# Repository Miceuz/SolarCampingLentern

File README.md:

# Open source Solar Camping Lantern

## Background

I started seeing a lot of disposable electronic cigarettes being used. As everyone knows, those devices contain perfectly rechargeable LiPo battery. And I've seen them thrown away everywhere - on streets, in general waste thrash cans, etc. While a lot of my friends have successfully refilled juice and re-charged the battery, the devices are not built to last - heating coil dies after several re-uses anyway. I have decided to look for a way to recycle those batteries. 

So I have decided to make a lantern for my camping needs and also investigate a product parameter space. The idea popped in to my mind during a summer music festival, actually. When you camp with your friends and need a bit of extra light in the camp at night. It was a sunny summer, so of course I had to have it solar powered. Provided unlimited supply of batteries, can it be self sufficient in it's power needs just from solar energy while still being manageable in camp environment?

It's always a good idea to check what's available at the market. Maybe there is a product on the market that does just that? Just a piece of my expenses, not worth spending my time?

## Initial requirements

 * Light output: ~100lm
 * Run time: min 4h
 * Battery: LiPo 3.7V ~2000mAh
 * Charging time: 6h

I have gauged the amount of needed light from my Lumilight pocket torch I have lost and my "cyclope" torch from Decathlon I got this year. 100lm is not a huge amount of light but still not that bad - it's enough to see people and stuff around, human eye is logarithmic and adapts to low light conditions.

Run time is a modest guess from a festival scenario - you might need light from 11 at night to 3 in the morning, roughly.

Charging time is a lazy day camping, maybe I will remember to pull it out and put on a sun sometime. It's not full effective sun time, just general time the device spends in sun semi-kinda-charging.

## Case studies

### [BioLite SunLight 100](https://www.bioliteenergy.com/products/sunlight-100?variant=1142597386254)

  * Light output: 100lm max
  * Battery: 750mAh LiPo
  * Run time: 3h
  * Solar pannel: 0.45W
  * Charging time: 7h
  * Dimensions: 85x86x23 mm
  * Weight: 95g
  * Price: 20$

### [MPOWERD Luci Outdoor 2.0](https://mpowerd.com/products/luci-outdoor-2-0-f2017)

 * Light output: 75lm
 * Battery: 1000mAh
 * Run time: 6h
 * Charging time: 7h
 * Dimensions: 127mm dia, 25mm height
 * Weight: 125g
 * Price: 24$

### [MPowerd Luci Solar String Lights](https://mpowerd.com/products/string-lights)

 * Light output: 100lm
 * Battery: 2000mAh
 * Charging time: 16h
 * Run time: 5h
 * Dimensions: 127mm dia, 50mm height
 * Weight: 320g
 * Price: 50$

There are devices that target the same light output I want. Some of these specifications are inferred as not all manufacturers provide all the information I needed. SunLight 100 does almost exactly what I want, but solar battery this size barely will produce 8.3Wh needed in 7h of charging time. All in all solar in all of these products seems to be a nice addition to USB charging, not the main power provider. 

Also I have bought some not-so-cheap crap from local hardware store that pretended like it can do what I want, but solar battery was total crap in those, outputting mere single digit milli-amps.

Thus, I have easily convinced myself that this is well worth as a hobby project. Besides, had to use those batteries up! So, with the battery sourcing question sorted out, let's not think about price too much and look what happens if we push on the light output efficiency and solar input efficiency.

## Design

### MPPT options

 * SPV1040T
 * ADP5090ACPZ-2-R7
 * BQ24650
 * [MPPT Solar Panel Controller with DC Converter](https://www.tindie.com/products/electronicstore/mppt-solar-panel-controller-with-dc-converter-2)

In the times of supply chain collapse, choosing a MMPT capable converter chip for storing solar energy to the battery was not an easy thing. They all are either not available or expensive. Luckily I have stumbled on this board by [PC Tech](https://www.tindie.com/stores/electronicstore/) featuring CN3791. Basically this project could have ended just there, as this board was all I needed - I have made my first prototype using it. Although I had to extract a bit more efficiency by having a dedicated led driver, also add some computer control to the thing. 

### Light Source

 * L130-4070003000W21 - Vf = 6V, I = 100mA, Light output = 100lm

It's one of the most efficient LEDs available at electronic distributors at the time. What's interesting and handy is that it's practically voltage controlled - it has a nice shallow IV curve. Provided you extract the heat from them though. They will happily do 100lm at 0.6W, the efficiency is even higher if you run them at half the rating. That's why I have doubled them up in my design.

Also I have decided to throw in a red light source, to see if it might be usable too. Red light does not dazzle humans too much, so it makes a good low level standby light source for the night. I did not want to add additional complication of channel switching for led driver chip, thus decided to power red led directly from MCU pin.

### Photovoltaics

 * [Solar panel](https://www.evita.lt/u-9045-saules-baterijos-modulis-6v-3-5w-165x135mm?search=saul%C4%97s) 6V, 3.5W

These panels, available at local suppliers, looked like a good trade-off between size and output power. Besides, not a lot to choose from, really. I have measured them and they were outputting the rated power, but it dropped drastically with non-perfect orientation to the sun, thus it has to be de-rated significantly. I have guesstimated MPPT point of the panel to be somewhere at 80% of it's open circuit voltage and measured about the same with a potentiometer hooked up to it.

### Power

**If you replicate this design, be warned that battery failure is a risk to be considered!**

 * Battery: 3.7 LiPo, capacity varies: 1.4Wh, 1.85Wh, total capacity up to 11Wh
 * MCU powered directly from battery
 * DC-DC led driver - MCP1664

Batteries are re-used from electronic cigarettes. I don't really know if they retain their safety ratings after they have been re-charged, but people around are re-charging them and I've heard of no fires happening. 

They come with a protection board and I have tried shorting and over-discharging them - seem to work fine, also I've seen my friends ridiculously abusing them with high charge currents on par of 3C. Their longevity is to be proven though as they might not be optimized for a lot of re-charge cycles, but it seems their safety is on par with standards mandatory with CE marking. I am happy to delay their travel to a landfill or a recycler.  

### Operational parameters

 * Energy consumed: 0.1A * 6V * 4h = 2.4Wh
 * Solar power available: 3.5W minus conversion losses
 * Light output: 120lm

It has plenty of solar - 1h of perfect sunlight should provide enough of charge for 4 required hours. Seems to make sense to have more battery capacity, but there is a small trade-off with the weight. It will be interesting to experiment with battery sizes and see what run times are achievable.

### Mechanical construction

Size and shape of the device is dictated by the solar panel. Since I wanted a lot of solar power, I knew I will not be able to make it as compact as commercially available devices. Also mechanical side of things is not my strength, so I went for a simple flat panel. One of use cases for such a light would be as a coaster for a water bottle - that makes a pretty nice low effort table light. Also I've added 4 holes to attach the lantern with rope - to a branch or a tarp. 

All assembly is glue based (blergh!). Batteries are glued to the PCB. PCB is glued and soldered to the solar panel. Both the solar panel and plexiglass are glued to a 3D printed plastic frame.

Considering the usage scenario, of course it should have some level of ingress protection. Provided all glue seams are tight (sic!), the only place for water to seep in is through a button hole. I am going to experiment with printing of the frame from flexible plastics and have the button hole closed, but for the first revision there's going to be a small seam between hole and plunger and IPX6 rated button behind it.

### MCU and software

I have chosen my beloved attiny441 - I have a stock of them and I am used to them and it's a relief to spend some time in a simple naive world of 8-bit microcontrollers. It's pretty low power too.

Software functions:

 * On/Off
 * Different levels of lighting
 * Cycle through white and red leds
 * Indicate battery level via charlieplexed leds
 * Auto level reduction on low battery [todo]
 * Fade everywhere [todo]
 * Sky's the limit, what can you do with a single button interface?

### Bells and whistles

 * Charlieplexed leds for battery level indication

### Weight analysis

| Item | Weight, g |
|------|-----------|
| 3.5W solar panel | 96 |
| Plexiglass | 73 |
| Frame | 56 |
| PCB 0.8mm | 36 |
| Battery 380mAh 7g, 3pack | 22 |
| Electronic components | 4 |
| Glue | 10 |
| **Total** | **297** |

## BOM Price analysis

| Item | Price, € |
|------|----------|
| Solar panel | 13 |
| Electronic components | 6.3 |
| PCB | 5.1 |
| Frame | 2 |
| Plexiglass | 0.6 |
| Batteries | 0 |
| **Total** | **27** | 

Prices are for a small batch of 10 units.

## Final specifications

 * Light output: 120lm
 * Battery: LiPo 3.7V up to 4000mAh 
 * Run time: >4h
 * Solar pannel: 3.5W
 * Charging time for 4h run time: 1h (perfect sun conditions)
 * Dimensions: 193x163x15 mm
 * Weight: 297g
 * BOM Price: 27€

## Conclusion

I took me 3 PCB iterations to get it right, I had to adjust a button position so it's easier to find in the dark, also I had to spread battery level indication leds along the edge so they would be distinguishable behind the plexiglass. Finally I have used 4 while leds instead of two, also spaced out as the single light source was a bit too strong. 

Weight is a concern, but here I am limited to materials I have access to. I have made some improvements by using a 0.8mm PCB, maybe I can make the frame lighter, but the real limiting factors are solar pannel and plexiglass.

I have tried using the first prototype while camping at sunny autumn and it proved to be working very well. Working time with 870mAh battery was a little too short for long autumn evenings at full 100lm, but it was able to fully charge during the next day. Later I brought the panel to a rainy camping trip in December. Panel was barely charging the 5.5Ah battery, but it held almost two evenings allowing us to set up camp, prepare wood and chill under the red light in addition to fire. I think it's not much useful for rainy winter in Easter Europe, but it will be a perfect light for summer camping.

## Licence

[CERN Open Hardware Licence Version 2 - Strongly Reciprocal](https://ohwr.org/cern_ohl_s_v2.txt)

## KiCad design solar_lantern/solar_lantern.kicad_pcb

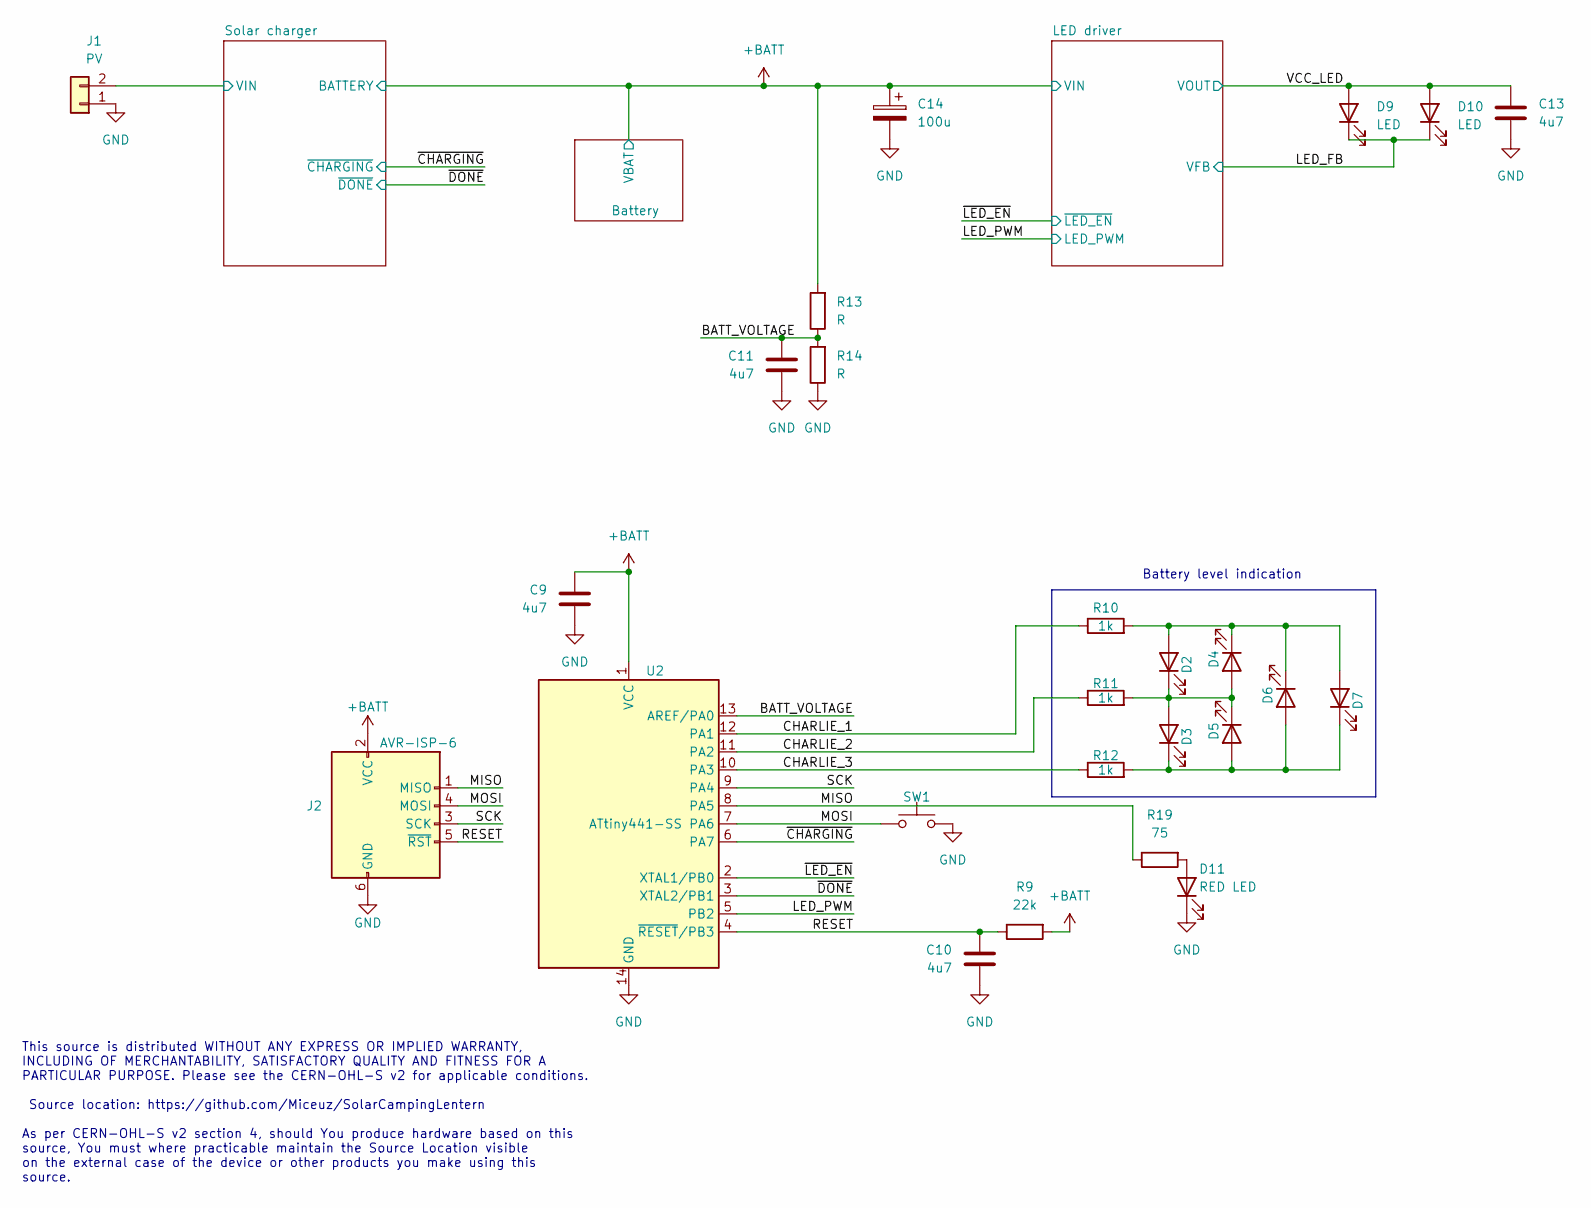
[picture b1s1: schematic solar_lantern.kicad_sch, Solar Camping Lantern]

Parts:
C9, C10, C11, C13: 4u7; C_0603_1608Metric
C14: 100u; CP_Elec_6.3x5.4_Nichicon; PartNo EEV107M016S9GAA
D2, D3, D4, D5, D6, D7: LED; D_0603_1608Metric
D9, D10: LED; DS207; PartNo L130-4070003000W21
D11: RED LED; LED_PLCC-2; PartNo CLM1B-RKW-CUbVbAA3
J1: PV; PinHeader_1x02_P2.54mm_Vertical
J2: AVR-ISP-6; PinHeader_2x03_P2.54mm_Vertical
R9: 22k; R_0603_1608Metric
R10, R11, R12: 1k; R_0603_1608Metric
R13, R14: R; R_0603_1608Metric
R19: 75; R_0603_1608Metric
SW1: SW_Push; SW_Push_1P1T_NO_6x6mm_H9.5mm; PartNo 1571407-2
U2: ATtiny441-SS; SOIC-14_3.9x8.7mm_P1.27mm

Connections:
+BATT: C9.2, C14.1, J2.2 (VCC), R9.2, R13.2, U2.1 (VCC); also elsewhere on the board
/BATT_VOLTAGE: C11.2, R13.1, R14.2, U2.13 (AREF/PA0)
/CHARLIE_1: R10.1, U2.12 (PA1)
/CHARLIE_2: R11.1, U2.11 (PA2)
/CHARLIE_3: R12.1, U2.10 (PA3)
/LED_FB: D9.1 (K), D10.1 (K); also elsewhere on the board
/LED_PWM: U2.5 (PB2); also elsewhere on the board
/MISO: J2.1 (MISO), R19.1, U2.8 (PA5)
/MOSI: J2.4 (MOSI), SW1.1, U2.7 (PA6)
/RESET: C10.2, J2.5 (~RST), R9.1, U2.4 (~RESET/PB3)
/SCK: J2.3 (SCK), U2.9 (PA4)
/Solar charger/VIN: J1.2; also elsewhere on the board
/VCC_LED: C13.1, D9.2 (A), D10.2 (A); also elsewhere on the board
/~CHARGING: U2.6 (PA7); also elsewhere on the board
/~DONE: U2.3 (XTAL2/PB1); also elsewhere on the board
/~LED_EN: U2.2 (XTAL1/PB0); also elsewhere on the board
GND: C9.1, C10.1, C11.1, C13.2, C14.2, D11.2 (K), J1.1, J2.6 (GND), R14.1, SW1.2, U2.14 (GND); also elsewhere on the board
unnamed: D2.1 (K), D3.2 (A), D4.2 (A), D5.1 (K), R11.2
unnamed: D2.2 (A), D4.1 (K), D6.1 (K), D7.2 (A), R10.2
unnamed: D3.1 (K), D5.2 (A), D6.2 (A), D7.1 (K), R12.2
unnamed: D11.1 (A), R19.2

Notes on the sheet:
This source is distributed WITHOUT ANY EXPRESS OR IMPLIED WARRANTY, INCLUDING OF MERCHANTABILITY, SATISFACTORY QUALITY AND FITNESS FOR A PARTICULAR PURPOSE. Please see the CERN-OHL-S v2 for applicable conditions. Source location: https://github.com/Miceuz/SolarCampingLentern As per CERN-OHL-S v2 se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
Battery level indication

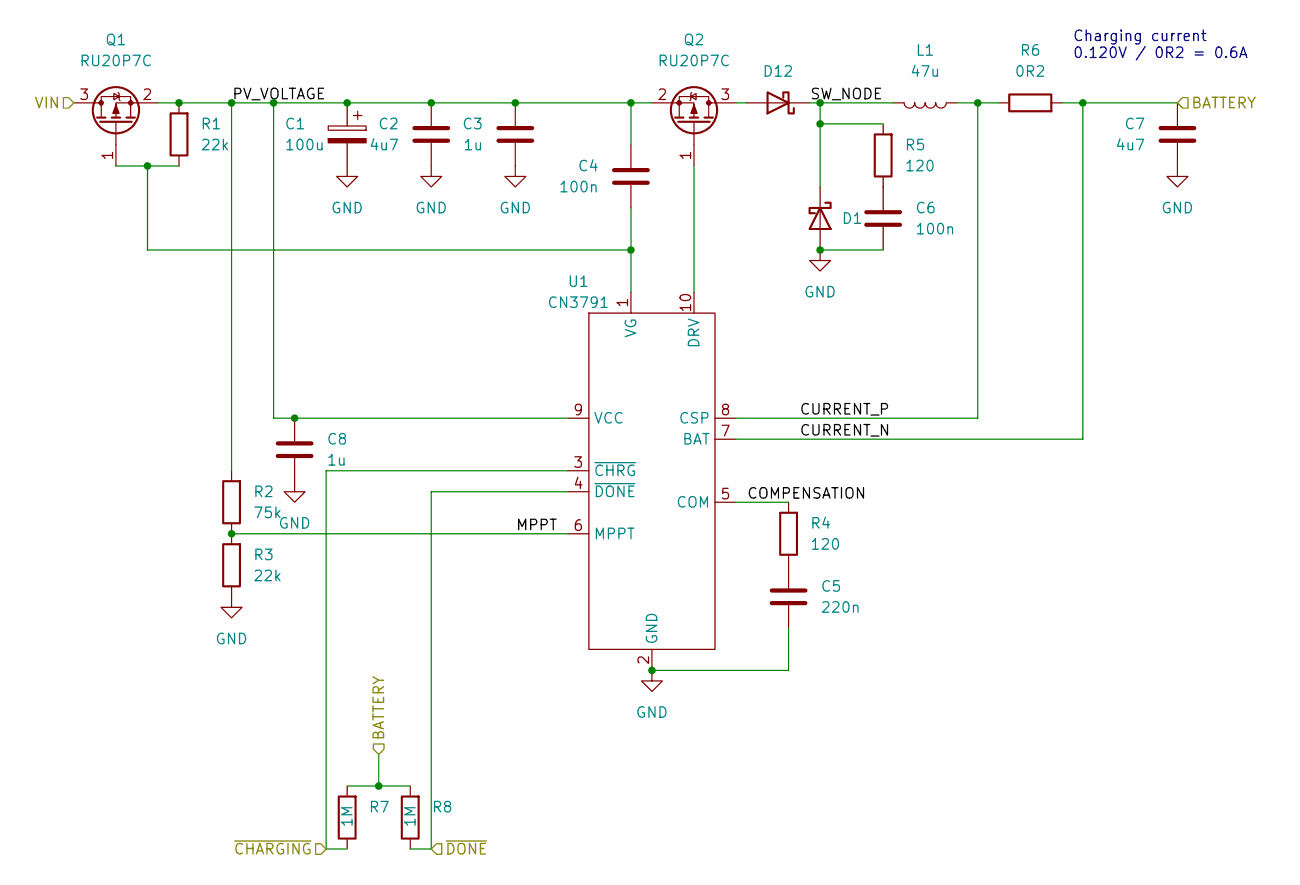
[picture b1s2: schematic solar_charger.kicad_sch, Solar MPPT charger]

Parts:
C1: 100u; CP_Elec_6.3x5.4_Nichicon; PartNo EEV107M016S9GAA
C2, C7: 4u7; C_0603_1608Metric
C3, C8: 1u; C_0402_1005Metric
C4, C6: 100n; C_0603_1608Metric
C5: 220n; C_0603_1608Metric
D1, D12: D_Schottky; D_SOD-323
L1: 47u; L_Coilcraft_XAL60xx_6.36x6.56mm
Q1, Q2: RU20P7C; SOT-23
R1, R3: 22k; R_0603_1608Metric
R2: 75k; R_0603_1608Metric
R4, R5: 120; R_0603_1608Metric
R6: 0R2; R_2512_6332Metric
R7, R8: 1M; R_0603_1608Metric
U1: CN3791; SSOP-10_3.9x4.9mm_P1.00mm

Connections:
+BATT: C7.2, R6.2, R7.2, R8.2, U1.7 (BAT); also elsewhere on the board
/Solar charger/COMPENSATION: R4.2, U1.5 (COM)
/Solar charger/CURRENT_P: L1.2, R6.1, U1.8 (CSP)
/Solar charger/MPPT: R2.1, R3.2, U1.6 (MPPT)
/Solar charger/PV_VOLTAGE: C1.1, C2.2, C3.2, C4.2, C8.2, Q1.2 (S), Q2.2 (S), R1.2, R2.2, U1.9 (VCC)
/Solar charger/SW_NODE: D1.1 (K), D12.1 (K), L1.1, R5.2
/Solar charger/VIN: Q1.3 (D); also elsewhere on the board
/~CHARGING: R7.1, U1.3 (~CHRG); also elsewhere on the board
/~DONE: R8.1, U1.4 (~DONE); also elsewhere on the board
GND: C1.2, C2.1, C3.1, C5.1, C6.1, C7.1, C8.1, D1.2 (A), R3.1, U1.2 (GND); also elsewhere on the board
unnamed: C4.1, Q1.1 (G), R1.1, U1.1 (VG)
unnamed: C5.2, R4.1
unnamed: C6.2, R5.1
unnamed: Q2.1 (G), U1.10 (DRV)
unnamed: D12.2 (A), Q2.3 (D)

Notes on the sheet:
Charging current 0.120V / 0R2 = 0.6A

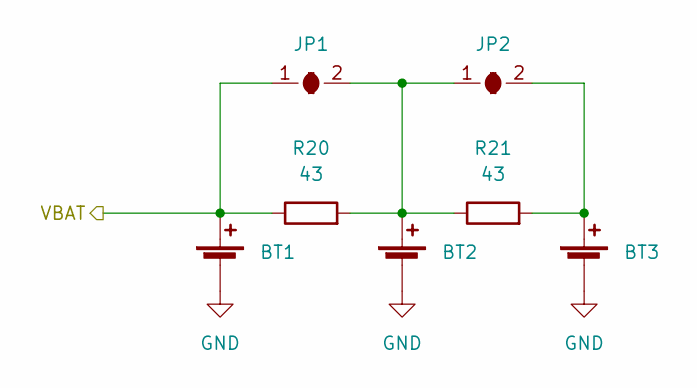
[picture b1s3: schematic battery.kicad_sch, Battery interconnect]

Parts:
BT1, BT2, BT3: Battery_Cell; PinHeader_1x02_P2.54mm_Vertical
JP1, JP2: SolderJumper_2_Open; SolderJumper-2_P1.3mm_Open_TrianglePad1.0x1.5mm
R20, R21: 43; R_0603_1608Metric; PartNo SDR03EZPJ430

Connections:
+BATT: BT1.1 (+), JP1.1 (A), R20.1; also elsewhere on the board
GND: BT1.2 (-), BT2.2 (-), BT3.2 (-); also elsewhere on the board
unnamed: BT2.1 (+), JP1.2 (B), JP2.1 (A), R20.2, R21.1
unnamed: BT3.1 (+), JP2.2 (B), R21.2

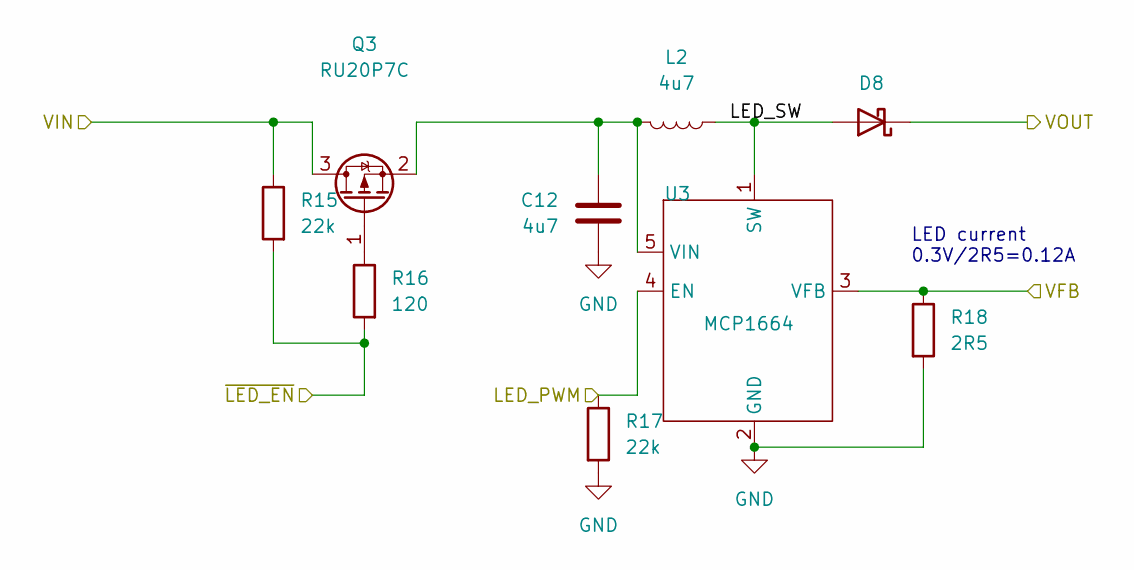
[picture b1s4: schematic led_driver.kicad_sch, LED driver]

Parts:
C12: 4u7; C_0603_1608Metric
D8: D_Schottky; D_SOD-323
L2: 4u7; L_Taiyo-Yuden_MD-4040; PartNo VLCF4020T-4R7N1R2
Q3: RU20P7C; SOT-23
R15, R17: 22k; R_0603_1608Metric
R16: 120; R_0603_1608Metric
R18: 2R5; R_0805_2012Metric; PartNo CRCW08052R49FKEA
U3: MCP1664; SOT-23-5

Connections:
+BATT: Q3.3 (D), R15.1; also elsewhere on the board
/LED driver/LED_SW: D8.2 (A), L2.2, U3.1 (SW)
/LED_FB: R18.1, U3.3 (VFB); also elsewhere on the board
/LED_PWM: R17.1, U3.4 (EN); also elsewhere on the board
/VCC_LED: D8.1 (K); also elsewhere on the board
/~LED_EN: R15.2, R16.2; also elsewhere on the board
GND: C12.1, R17.2, R18.2, U3.2 (GND); also elsewhere on the board
unnamed: C12.2, L2.1, Q3.2 (S), U3.5 (VIN)
unnamed: Q3.1 (G), R16.1

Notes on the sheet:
LED current 0.3V/2R5=0.12A

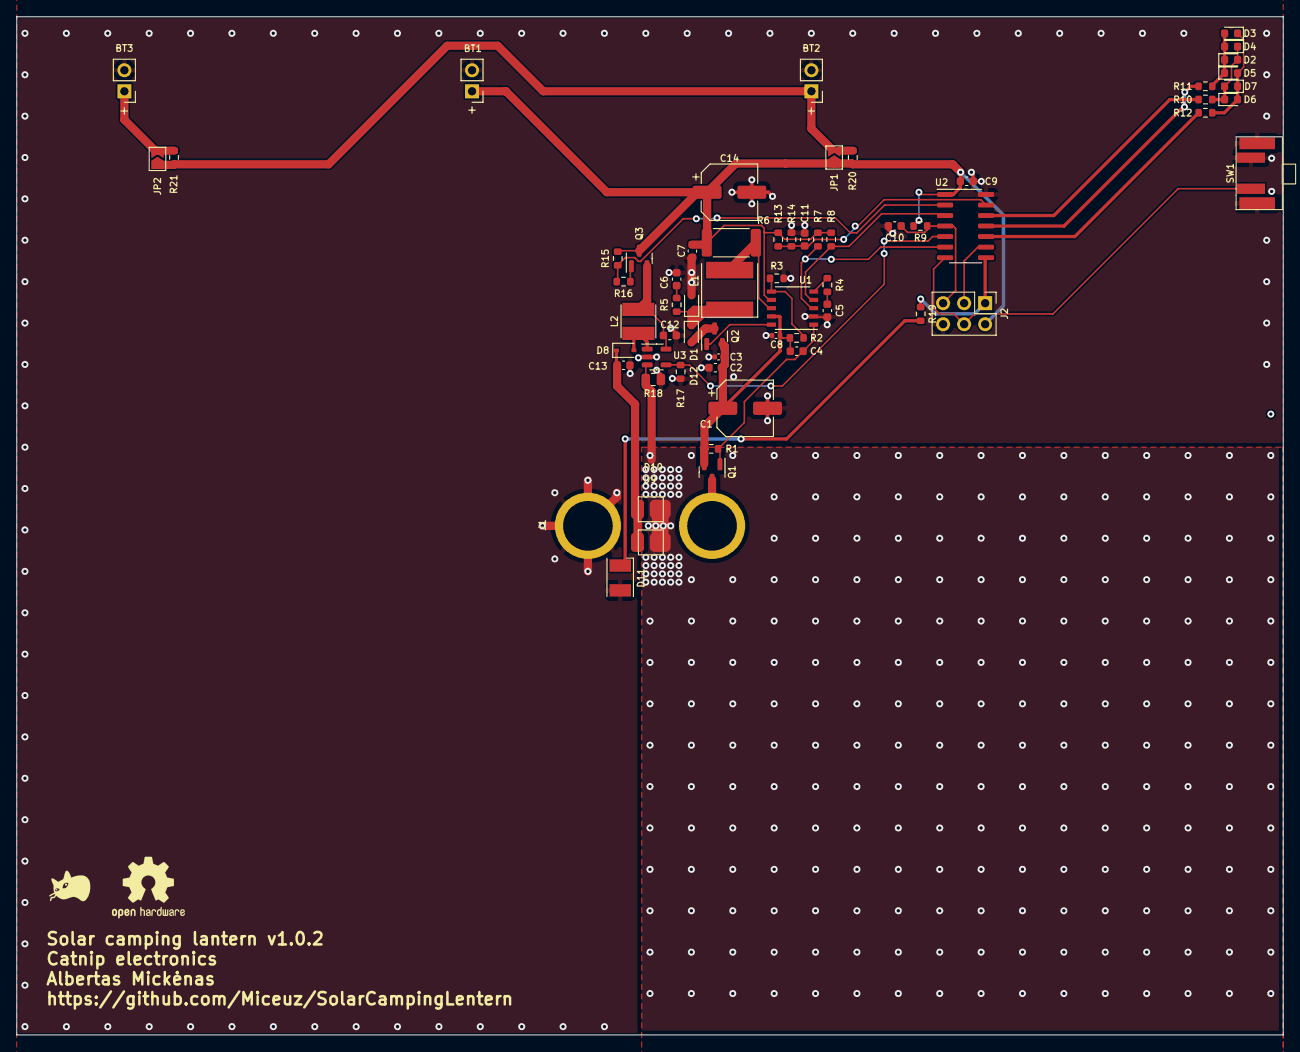
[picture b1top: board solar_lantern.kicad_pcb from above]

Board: 2 copper layers, 153.0 x 123.0 mm, 63 parts (0 on the bottom side), 36 nets.

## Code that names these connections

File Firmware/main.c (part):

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    896, 904, 912, 920, 929, 937, 945, 954, 962, 971, 980, 988, 997, 1005, 1014,
    1023};

#define BUTTON PA6
#define LED_WHITE_EN PB0
#define LED_WHITE_PWM PB2
#define LED_RED PA5

#define BUTTON_DEBOUNCE_INTERVAL_MS 10
uint32_t buttonDebounceTs = 0;
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inline static void sleep() {
  buttonReset(&button);

  // DDRA |= _BV(PA0);
  // PORTA &= ~_BV(PA0);

  DDRA |= _BV(PA1);
  PORTA &= ~_BV(PA1);

  DDRA |= _BV(PA2);
  PORTA &= ~_BV(PA2);

  DDRA |= _BV(PA3);
  PORTA &= ~_BV(PA3);

  DDRA |= _BV(PA4);
  PORTA &= ~_BV(PA4);

  DDRA |= _BV(PA5);
  PORTA &= ~_BV(PA5);

  DDRA &= ~_BV(PA7);
  PUEA |= _BV(PA7);

  DDRB &= ~_BV(PB1);
  PUEB |= _BV(PB1);

  pinChangeIntEnable();
  set_sleep_mode(SLEEP_MODE_PWR_DOWN);
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  }
}

#define CHARLIE1 PA1
#define CHARLIE2 PA2
#define CHARLIE3 PA3

void charlie(uint8_t x) {
  switch (x) {
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
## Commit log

2021-09-28 Add documentation
2021-09-28 Add electronics design files
2021-09-28 Add mechanical files
2021-11-23 Make board smaller, Fix bad cap orientation, Add a diode to reduce quescient current
2021-11-23 Add basic firmware
2021-11-23 Add weight analysis
2021-12-30 Write blog
2021-12-30 Add battery level measurement and display
2021-12-30 Fix PCB thickness, add some measirements to PCB
2022-01-23 Add support for long press
2022-01-23 Reformat code stolen from Arduino
2022-01-23 Add a function to choose light output for white leds
2022-01-23 Nicen schematics a bit
2022-01-23 Ignore vscode
2022-01-23 Add more info to readme
2022-01-29 Formatting
2022-01-29 Add CERN-OHL_S licence
2022-01-29 Add shematics in PDF
2022-11-04 Make fade continue on repeated long press. Switch off instead of moving to another state after 3s timeout
2022-12-13 Fix a bunch of typos
2022-12-13 Add optimization calculations
2022-12-13 Fix more typos
2022-12-15 Add pics to description
2022-12-15 Reflect the last revision in the decsription

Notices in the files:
Firmware/main.c:
Copyright Albertas Mickėnas 2022
This source describes Open Hardware and is licensed under the CERN-OHL-S v2.
You may redistribute and modify this source and make products using it under
the terms of the CERN-OHL-S v2 (https://ohwr.org/cern_ohl_s_v2.txt).
As per CERN-OHL-S v2 section 4, should You produce hardware based on this
solar_lantern/solar_lantern.kicad_pcb:
SPDX-License-Identifier: CERN-OHL-S-2.0
